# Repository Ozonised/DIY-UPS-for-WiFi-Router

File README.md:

# DIY-UPS-for-WiFi-Router

A UPS for Wi-Fi routers and ONU with 4 hours of back-up.

# SPECIFICATIONS
Here is a breif table containing the main specs of the UPS:
| CATEGORY | VALUE |
| :---: | :---: | 
| Back-UP time | Upto 4 hours|
| No. of Output ports | 2 |
| Output Voltage | 12V(1A) & 9V(800mA) |
| Input Voltage | 12V |
| Battery Type | 2s-2p li-ion |
| Battery Voltage | 7.4V(nominal) |
| Battery Capacity | 4000mAH |

# POWER
Unlike many commercial devices, this DIY UPS utilises 2 * 12 volt adapter. One for powering the Router and ONU, and the other for charging the batteries.
The adapter connected to the female barrel port labelled ```12V-IN-MAIN``` powers both the router and ONU, while the one connected to the female barrel port labelled ```12-IN-2ND``` is used for the charging the battery.
However, using two adapters is not a must, the entire thing can be powered by a single 12 volt adapter. To do so follow these steps:
- Short the pads ```TP1``` & ```TP2``` on the bottomside of the PCB.
- Now, plug the 12V adapter to the female barrel port labelled ```12V-IN-2ND```.

### Note:
 When using a single 12V adpater to power as well as charge the batteries, do not plug the 12V adapter into the female barrel port labelled ```12V-IN-MAIN```. Use the port labelled ```12V-IN-2ND```. Also use an adapter rated at-least 1.5 amps(2A is preferrable).

# BATTERY PACK
The battery is a 2s 2p lithium-ion pack with a nominal voltage of 7.4 volts and a capacity of, 4000mAh approximately.
The batteries are managed by this HW-882 3 A BMS for 2s lithium-ion battery pack.
Soldering the components on the PCB is a straight forward as everything is labelled. This is why I decided to skip the soldering part and focus on the wiring of the battery pack and XL4015 to the PCB.

## WIRING OF THE BATTERY PACK

### Note:
Set the voltage and current on the XL4015 buck converter to 8.35 volts and 1.35 amps respectively before connecting it to the battery.

## WIRING BATTERY PACK TO THE PCB
Below are the steps to wire the battery pack and the XL4015 to the main PCB:
- The input from the battery connects to the srew terminal labelled ```BATT-IN```. 
- The input wires of the XL4015 plugs into the screw terminal labelled ```TO BATT```. 
### Note:
The positive side is marked by  ```+``` symbol beside screw terminal on the PCB.

# CHARGING SYSTEM
The batteries are charged by a XL4015 CC/CV 5A buck converter module, whose voltage and current must be set to 8.35 volts and 1.4 amps respectively.
The XL4015 module is powered by a 12V 2A adapter. If your 12V adapter is rated below 2A then lower the charging current on the buck converter to an appropriate level. Below are some reccommended charging current values in relation to the adapter's current rating:

| Adapter's Current Rating(A) | Charging Current(A) |
| :---: | :---: |
| 1 | 0.7 - 0.8 |
| 1.5 | 1 - 1.2 |
| 2 | 1.2 - 1.6 |

# PART LIST

| Part | Quantity |
| :---: | :---: |
| 0.1uF Cap | 2 |
| 220uF Cap | 1 |
| 470uF Cap | 1 |
| Female Barrel Jack | 4 |
| Male Barrel Jack | 4 |
| Screw Terminal_01x02 | 2 |
| XL6009 module | 1 |
| XL4015 CC/CV module | 1 |
| 7809 | 1 |
| Heat sink | 1 |
| SPST_Switch | 1 |
| HW-882 3 A BMS | 1 |
| 18650 2000mAH lion cell | 4 |
| 12V 2A adapter | 1 |
| 12V 1A adapter | 1 |

In additon to the items mentioned above, you will also need some other miscellaneous stuff like wires, etc.

# CREDITS:
I would like to take a moment to thank the YouTube channel [Open Green Energy](https://www.youtube.com/c/OpenGreenEnergy) for his video series on DIY UPS for WiFi Routers. They have been of huge help to me for the development of this project.

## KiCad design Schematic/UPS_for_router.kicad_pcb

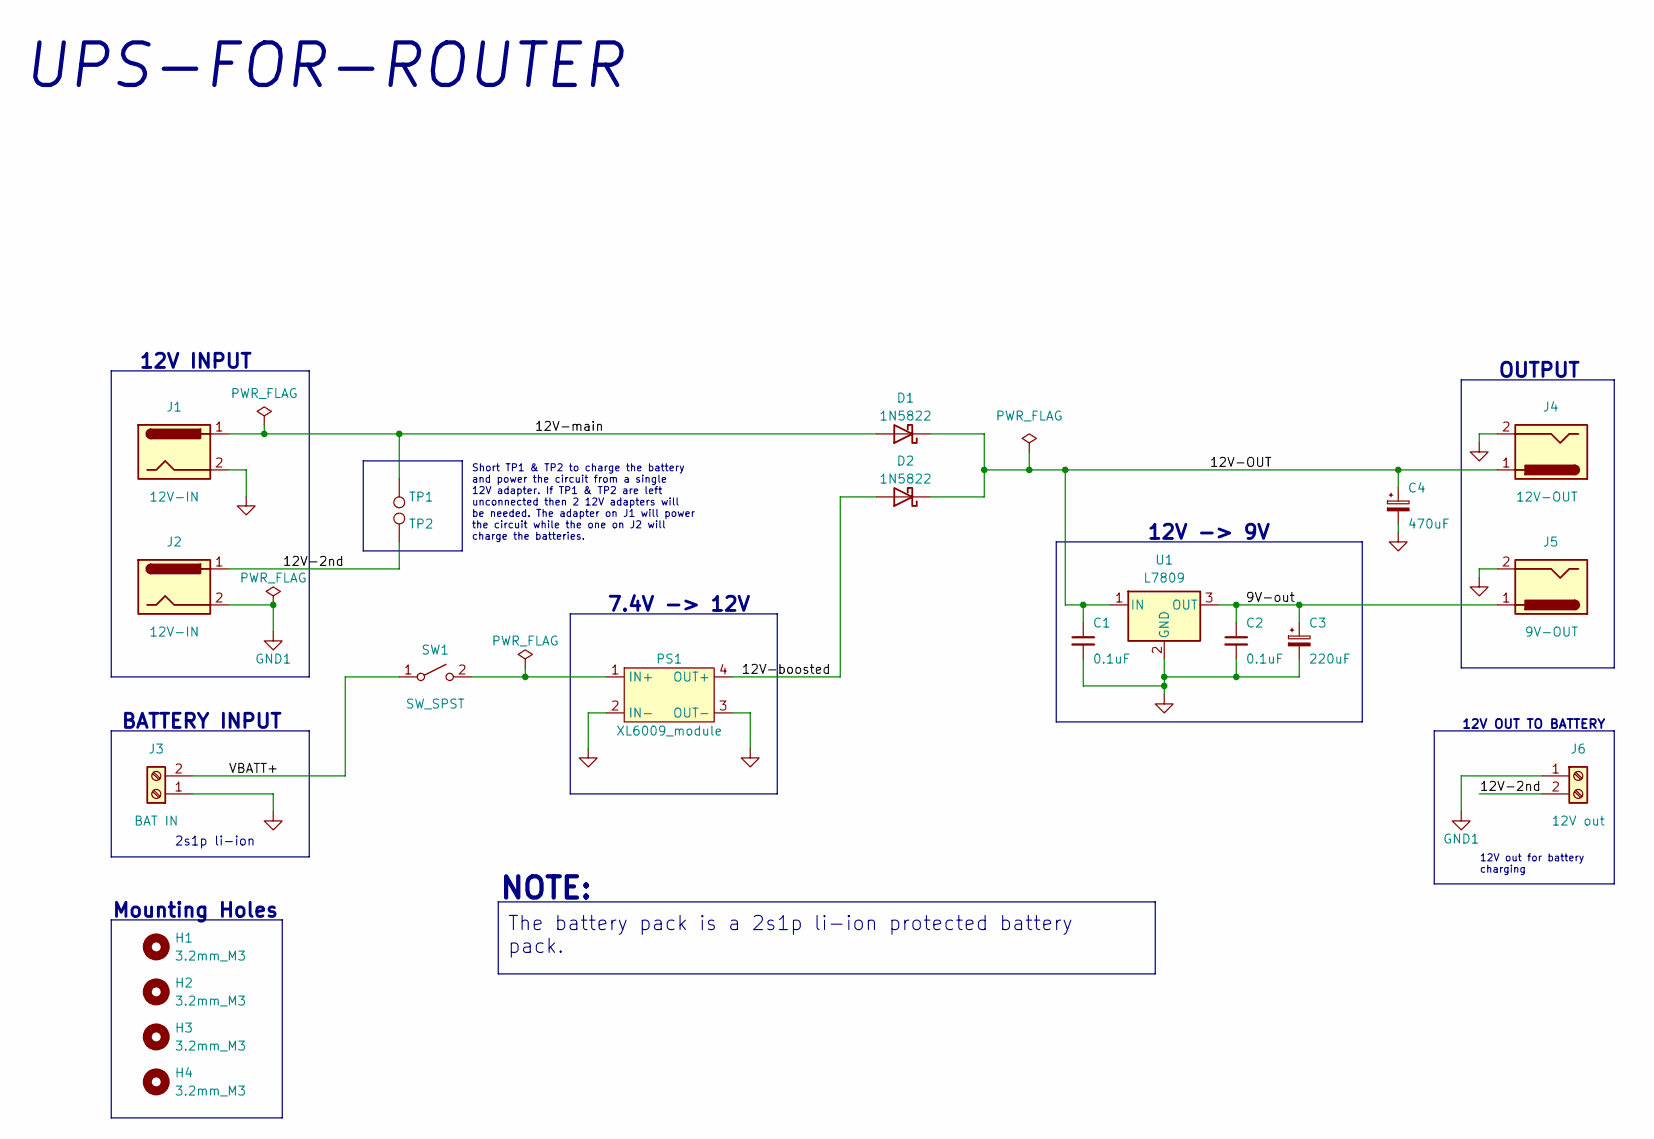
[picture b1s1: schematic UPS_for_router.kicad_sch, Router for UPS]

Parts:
C1, C2: 0.1uF; C_Disc_D5.0mm_W2.5mm_P2.50mm
C3: 220uF; CP_Radial_D6.3mm_P2.50mm
C4: 470uF; CP_Radial_D10.0mm_P5.00mm
D1, D2: 1N5822; D_DO-201AD_P15.24mm_Horizontal
H1, H2, H3, H4: 3.2mm_M3; MountingHole_3.2mm_M3
J1, J2: 12V-IN; BarrelJack_Horizontal
J3: BAT IN; TerminalBlock_Altech_AK300-2_P5.00mm
J4: 12V-OUT; BarrelJack_Horizontal
J5: 9V-OUT; BarrelJack_Horizontal
J6: 12V out; TerminalBlock_Altech_AK300-2_P5.00mm
PS1: XL6009_module
SW1: SW_SPST; TestPoint_2Pads_Pitch5.08mm_Drill1.3mm
TP1, TP2: SolderBridge; TestPoint_Pad_2.0x2.0mm
U1: L7809; TO-220-3_Vertical

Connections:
/9V-out: C2.1, C3.1, J5.1, U1.3 (OUT)
/12V-2nd: J2.1, J6.2, TP2.1
/12V-OUT: C1.1, C4.1, D1.1 (K), D2.1 (K), J4.1, U1.1 (IN)
/12V-boosted: D2.2 (A), PS1.4 (OUT+)
/12V-main: D1.2 (A), J1.1, TP1.1
/VBATT+: J3.2, SW1.1 (A)
GND: C1.2, C2.2, C3.2, C4.2, J1.2, J3.1, J4.2, J5.2, PS1.2 (IN-), PS1.3 (OUT-), U1.2 (GND)
GND1: J2.2, J6.1
unnamed: PS1.1 (IN+), SW1.2 (B)

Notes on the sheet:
12V OUT TO BATTERY
12V -> 9V
12V out for battery charging
12V INPUT
NOTE:
OUTPUT
Short TP1 & TP2 to charge the battery and power the circuit from a single 12V adapter. If TP1 & TP2 are left unconnected then 2 12V adapters will be needed. The adapter on J1 will power the circuit while the one on J2 will charge the batteries.
Mounting Holes
2s1p li-ion
7.4V -> 12V
UPS-FOR-ROUTER
The battery pack is a 2s1p li-ion protected battery pack.
BATTERY INPUT

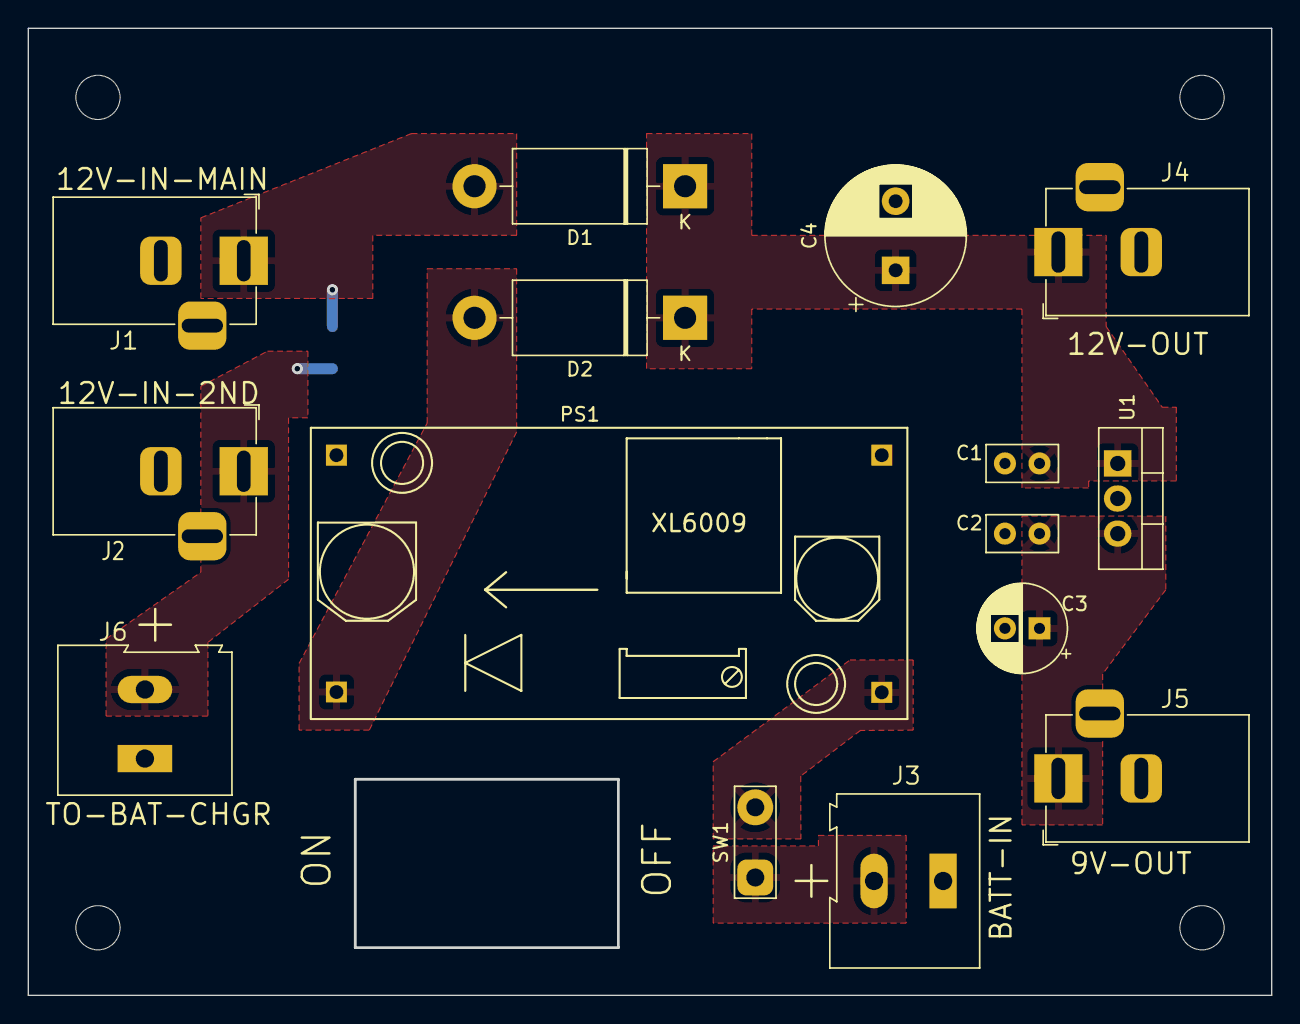
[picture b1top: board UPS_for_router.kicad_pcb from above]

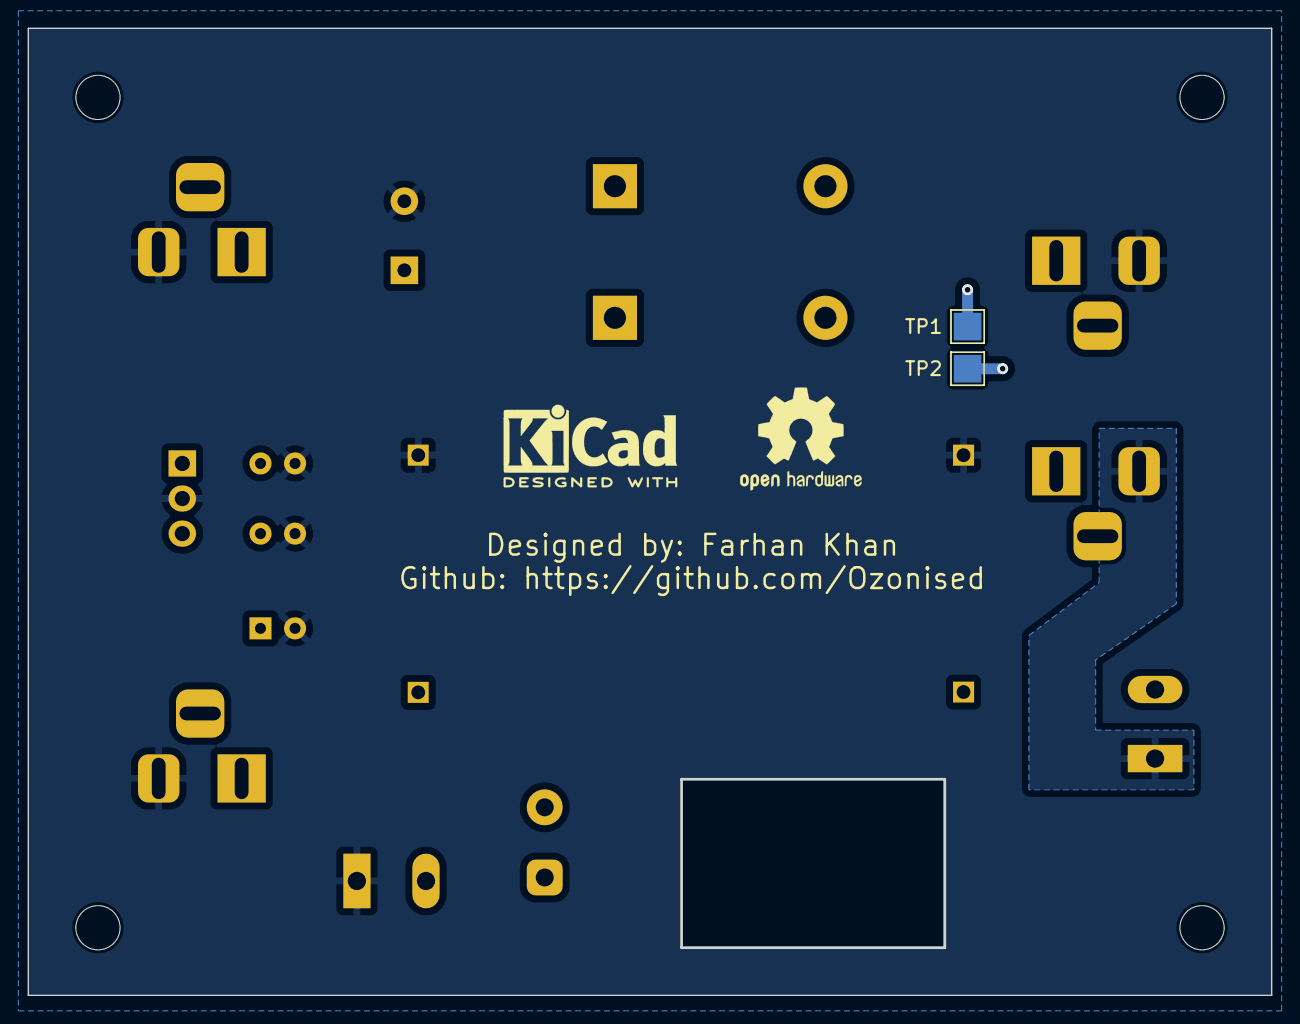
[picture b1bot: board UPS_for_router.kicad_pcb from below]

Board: 2 copper layers, 89.9 x 69.9 mm, 21 parts (2 on the bottom side), 9 nets.

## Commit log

2023-04-18 updated schematic and PCB
    removed relay and added diode as well as updated the PCB
2023-04-19 generated gerbers for rev2
2023-04-24 battery pack wiring
    added wiring diagram for battery pack
2023-04-24 updated battery pack wiring diagram
2023-05-13 addedprojects picture
2023-11-24 Update README.md
    Credits to open greeen energy
